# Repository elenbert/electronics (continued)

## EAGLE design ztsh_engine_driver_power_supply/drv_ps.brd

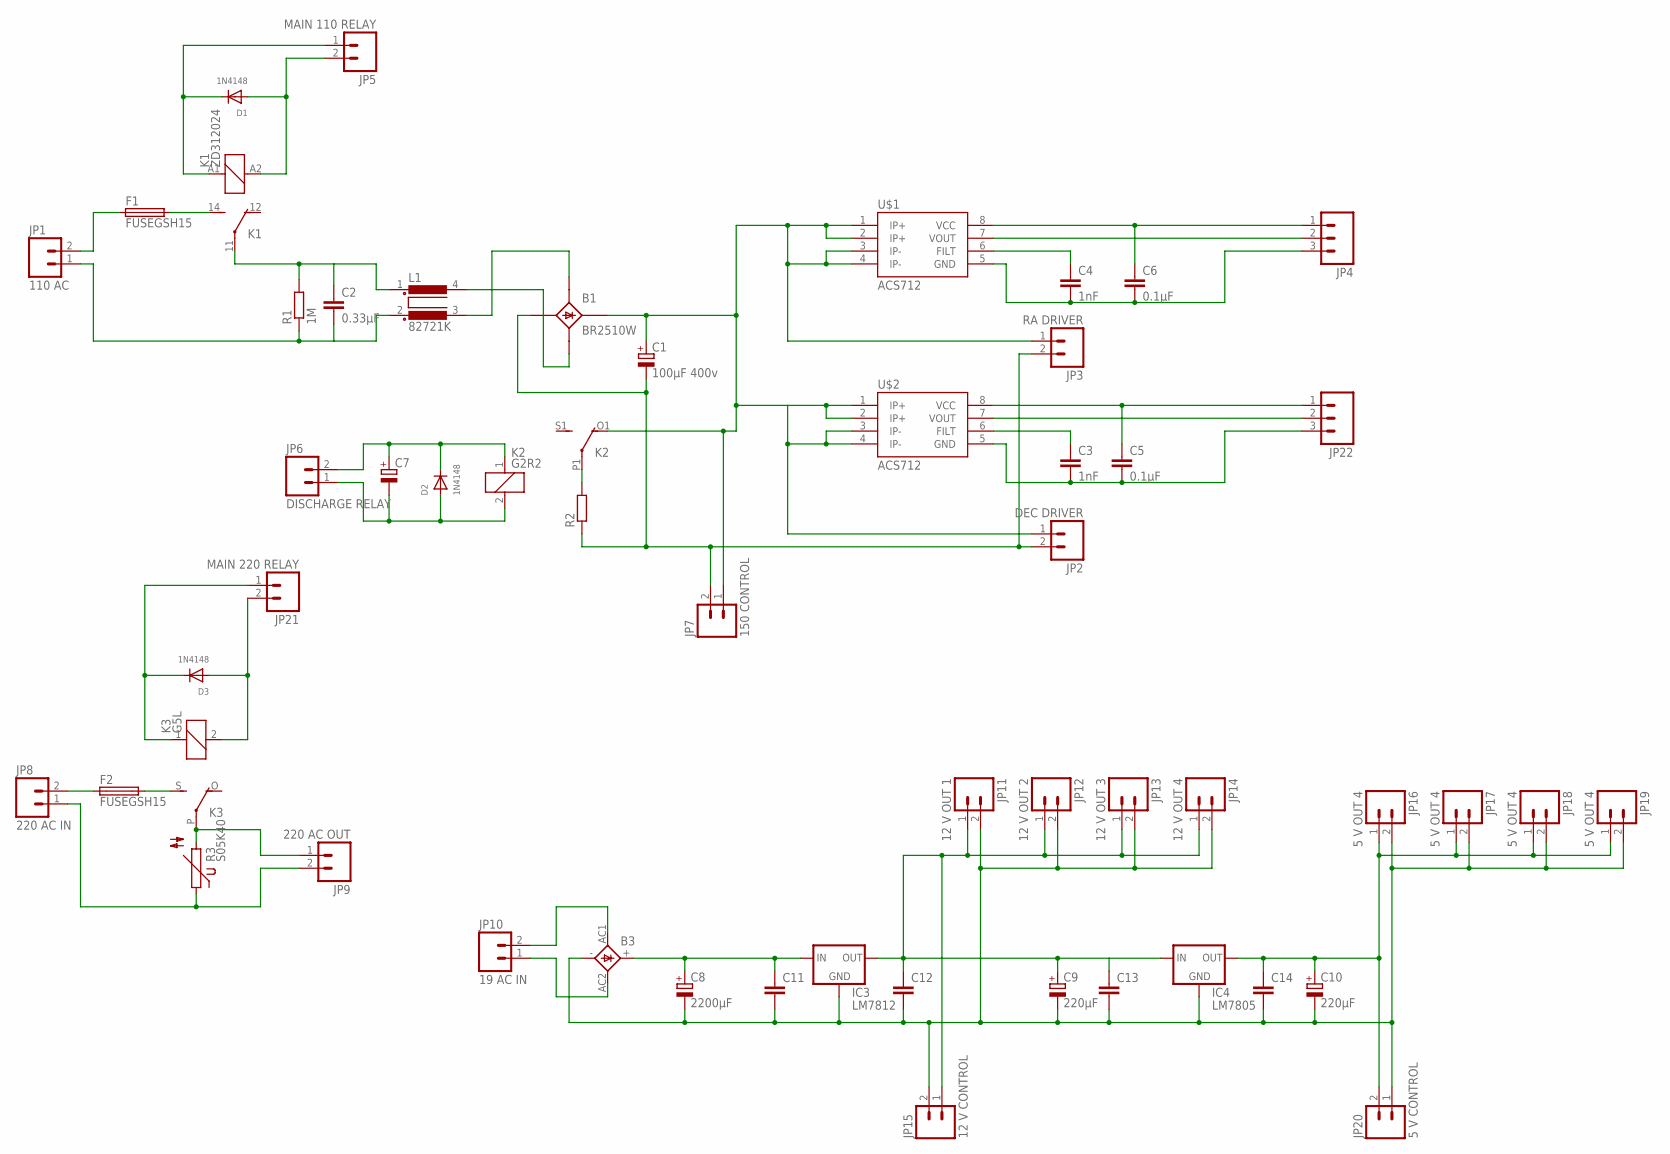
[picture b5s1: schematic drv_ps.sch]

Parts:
B1: BR2510W; B25A-
B3: GBPC1
C1: 100µF 400v; EB35D
C2: 0.33µF; C150-054X183
C3, C4: 1nF; C0805
C5, C6: 0.1µF; C0805
C7: CPOL-EUE2,5-6E; E2,5-6E
C8: 2200µF; E5-13
C9, C10: 220µF; E2,5-5
C11, C12, C13, C14: C-EUC0805; C0805
D1, D2, D3: 1N4148; DO-1N4148
F1, F2: FUSEGSH15; GSH15
IC3: LM7812; 78XXL
IC4: LM7805; 78XXL
JP1: 110 AC; SCREWTERMINAL-5MM-2
JP2: DEC DRIVER; SCREWTERMINAL-5MM-2
JP3: RA DRIVER; SCREWTERMINAL-5MM-2
JP4, JP22: M03POLAR; MOLEX-1X3
JP5: MAIN 110 RELAY; MOLEX-1X2
JP6: DISCHARGE RELAY; MOLEX-1X2
JP7: 150 CONTROL; MOLEX-1X2
JP8: 220 AC IN; SCREWTERMINAL-5MM-2
JP9: 220 AC OUT; SCREWTERMINAL-5MM-2
JP10: 19 AC IN; SCREWTERMINAL-5MM-2
JP11: 12 V OUT 1; JST-2-PTH-VERT
JP12: 12 V OUT 2; JST-2-PTH-VERT
JP13: 12 V OUT 3; JST-2-PTH-VERT
JP14: 12 V OUT 4; JST-2-PTH-VERT
JP15: 12 V CONTROL; 1X02
JP16, JP17, JP18, JP19: 5 V OUT 4; JST-2-PTH-VERT
JP20: 5 V CONTROL; 1X02
JP21: MAIN 220 RELAY; MOLEX-1X2
K1: ZD312024; ZD1
K2: G2R2
K3: G5L; G5LE
L1: 82721K
R1: 1M; 0411/15
R2: R-EU_VTA54; VTA54
R3: S05K40
U$1, U$2: ACS712; SO08

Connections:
5VCC: C10.+, C14.1, IC4.OUT, JP16.1, JP17.1, JP18.1, JP19.1, JP20.2
12VCC: C9.+, C12.1, C13.1, IC3.OUT, IC4.IN, JP11.1, JP12.1, JP13.1, JP14.1, JP15.1
19AC1: B3.AC2, JP10.1
19AC2: B3.AC1, JP10.2
110AC2: B1.AC2- (AC2), L1.4 (2)
110ACAF: F1.2, K1.14 (S)
110ACAR: C2.1, K1.11, L1.1, R1.2
110ACF1: B1.AC1- (AC1), L1.3 (4)
110ACG1: C2.2, JP1.1, L1.2 (3), R1.1
110ACPF: F1.1, JP1.2
110VC: B1.+1 (+), C1.+, JP2.1, JP3.1, JP7.1, K2.O1 (O), U$1.1 (IP+), U$1.2 (IP+), U$1.3 (IP-), U$1.4 (IP-), U$2.1 (IP+), U$2.2 (IP+), U$2.3 (IP-), U$2.4 (IP-)
AGND: B1.-1 (-), C1.-, JP2.2, JP3.2, JP7.2, R2.1
GND: B3.-, C8.-, C9.-, C10.-, C11.2, C12.2, C13.2, C14.2, IC3.GND, IC4.GND, JP11.2, JP12.2, JP13.2, JP14.2, JP15.2, JP16.2, JP17.2, JP18.2, JP19.2, JP20.1
unnamed: C4.1, U$1.6 (FILT)
unnamed: C4.2, C6.2, JP4.3, U$1.5 (GND)
unnamed: C3.1, U$2.6 (FILT)
unnamed: C6.1, JP4.1, U$1.8 (VCC)
unnamed: C3.2, C5.2, JP22.3, U$2.5 (GND)
unnamed: D1.C, JP5.1, K1.A1 (1)
unnamed: D1.A, JP5.2, K1.A2 (2)
unnamed: JP22.2, U$2.7 (VOUT)
unnamed: JP4.2, U$1.7 (VOUT)
unnamed: B3.+, C8.+, C11.1, IC3.IN
unnamed: C5.1, JP22.1, U$2.8 (VCC)
unnamed: K2.P1, R2.2
unnamed: C7.+, D2.C, JP6.2, K2.1
unnamed: C7.-, D2.A, JP6.1, K2.2
unnamed: JP9.1, K3.P, R3.2
unnamed: F2.1, JP8.2
unnamed: F2.2, K3.S
unnamed: JP8.1, JP9.2, R3.1
unnamed: D3.A, JP21.2, K3.2
unnamed: D3.C, JP21.1, K3.1

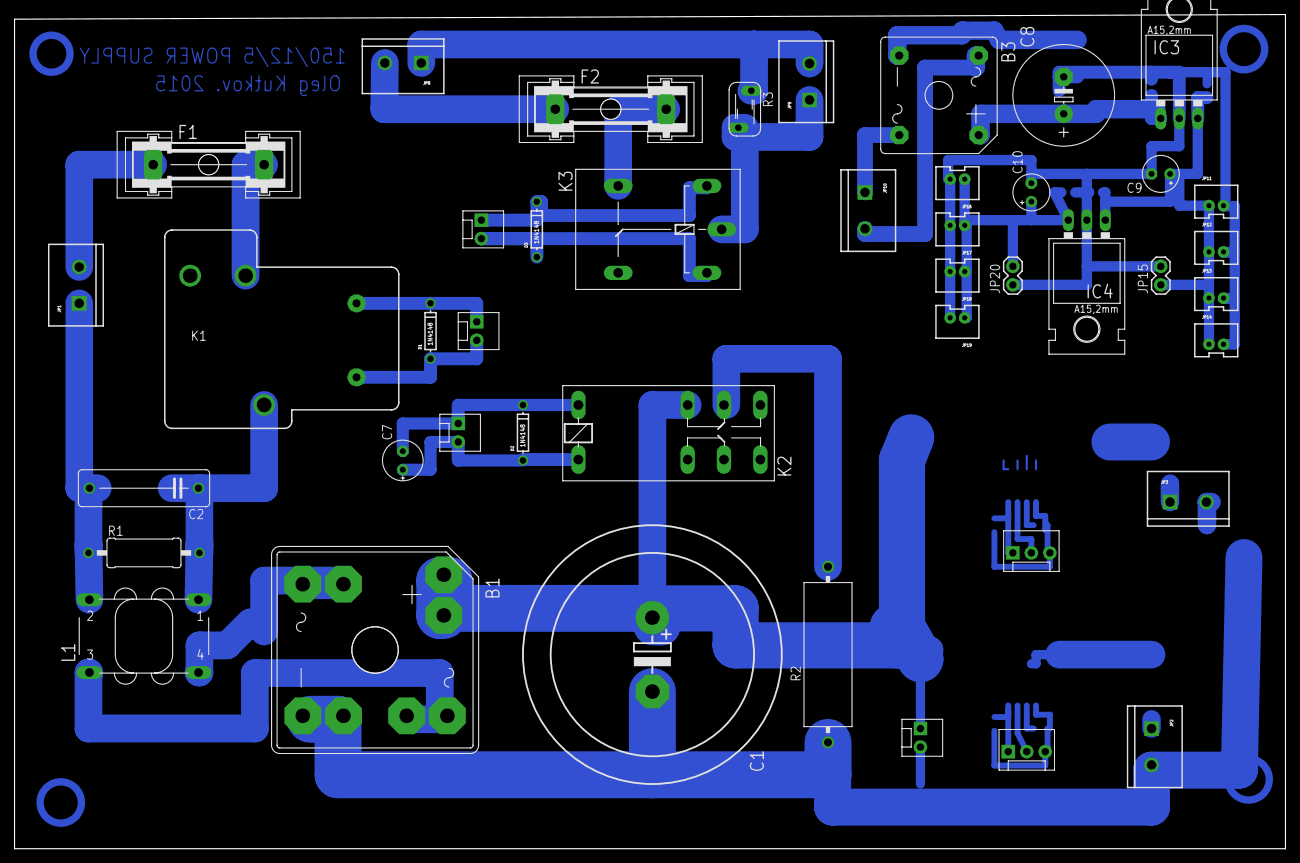
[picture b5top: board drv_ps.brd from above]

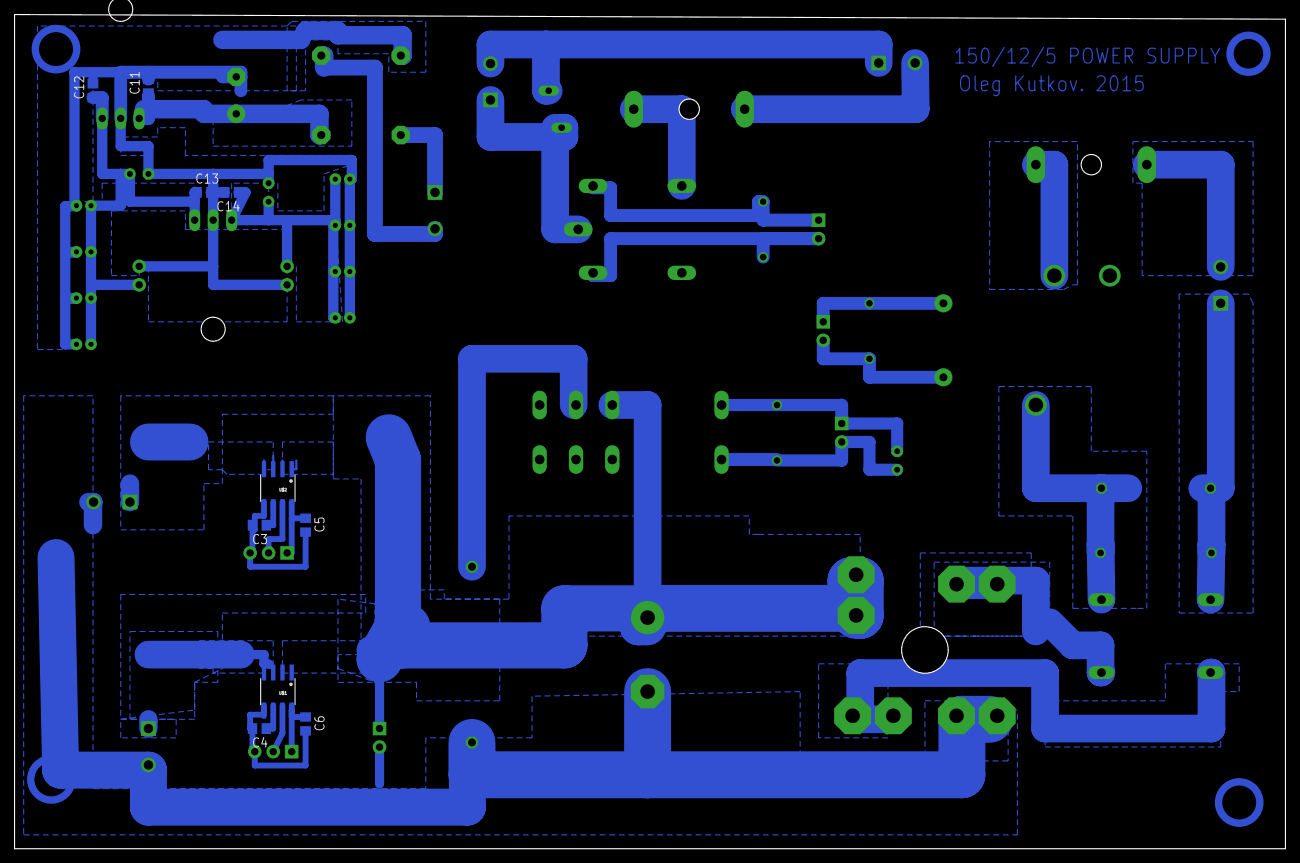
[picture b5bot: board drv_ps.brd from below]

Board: 2 copper layers, 174.6 x 114.6 mm, 54 parts (10 on the bottom side), 33 nets.

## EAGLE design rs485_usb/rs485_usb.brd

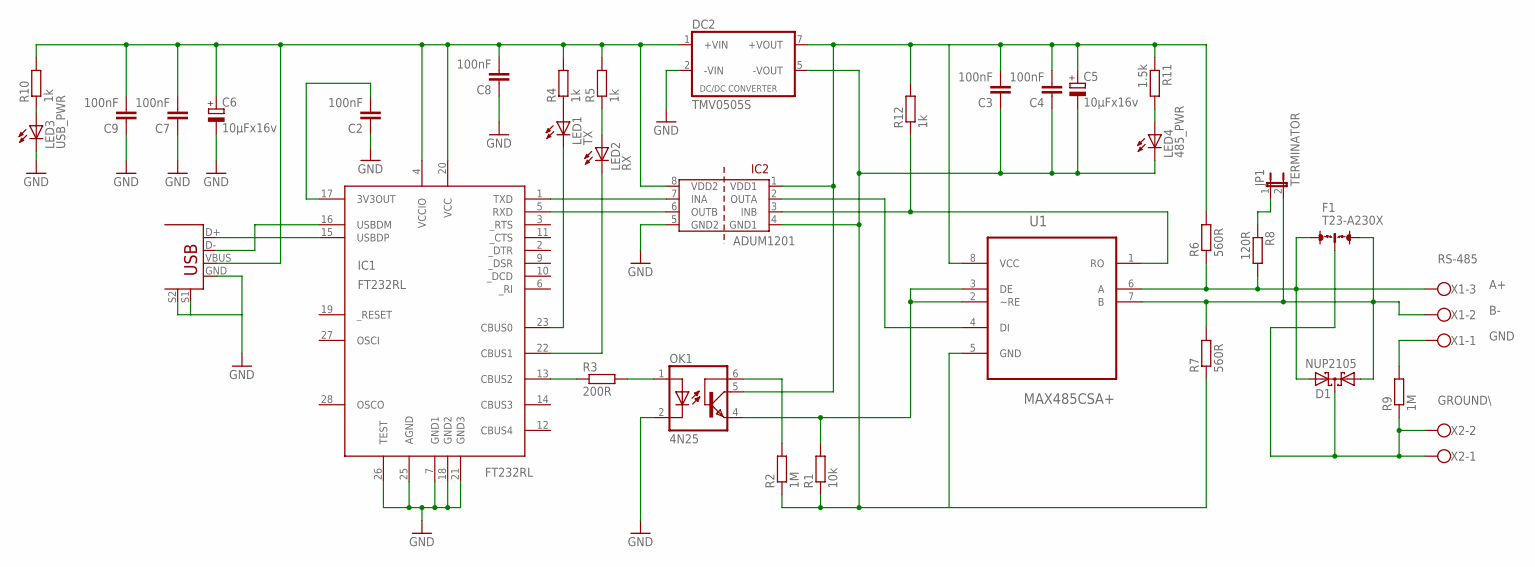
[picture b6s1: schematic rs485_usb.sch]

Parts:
C2: 100nF; C0603
C3, C4, C7, C8, C9: 100nF; C0805
C5, C6: 10µFx16v; E2,5-6E
D1: NUP2105; SOT23
DC2: TMV0505S; NMKXXXXSAC
F1: T23-A230X
IC1: FT232RL; SSOP28DB
IC2: ADUM1201; SO8
JP1: TERMINATOR; JP1
LED1: TX; LED3MM
LED2: RX; LED3MM
LED3: USB_PWR; LED3MM
LED4: 485_PWR; LED3MM
OK1: 4N25; DIL06
R1: 10k; 0204/5
R2: 1M; R0603
R3: 200R; R0603
R4, R5, R10, R12: 1k; R0805
R6, R7: 560R; R0603
R8: 120R; R0603
R9: 1M; 0207/2V
R11: 1.5k; R0805
U1: MAX485CSA+; SOIC127P600X175-8N
U$1: USB+SHIELD; USB-B-PTH
X1: W237-103
X2: W237-102

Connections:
GND: C2.1, C6.-, C7.1, C8.1, C9.1, DC2.2 (-VIN), IC1.7 (GND1), IC1.18 (GND2), IC1.21 (GND3), IC1.25 (AGND), IC1.26 (TEST), IC2.5 (GND2), LED3.K (C), OK1.2 (C), U$1.GND, U$1.S1, U$1.S2
GROUND: D1.3 (C), F1.2, R9.1, X2.1, X2.2
unnamed: IC1.15 (USBDP), U$1.D+
unnamed: IC1.16 (USBDM), U$1.D-
unnamed: C6.+, C7.2, C8.2, C9.2, DC2.1 (+VIN), IC1.4 (VCCIO), IC1.20 (VCC), IC2.8 (VDD2), R4.2, R5.2, R10.2, U$1.VBUS
unnamed: IC1.1 (TXD), IC2.7 (INA)
unnamed: IC1.5 (RXD), IC2.6 (OUTB)
unnamed: OK1.4 (EMI), R1.2, U1.2 (~RE), U1.3 (DE)
unnamed: IC2.2 (OUTA), U1.4 (DI)
unnamed: IC2.3 (INB), R12.1, U1.1 (RO)
unnamed: JP1.1, R8.1
unnamed: C3.2, C4.2, C5.+, DC2.7 (+VOUT), IC2.1 (VDD1), OK1.5 (COL), R6.2, R11.1, R12.2, U1.8 (VCC)
unnamed: OK1.6 (BAS), R2.2
unnamed: OK1.1 (A), R3.2
unnamed: IC1.13 (CBUS2), R3.1
unnamed: IC1.23 (CBUS0), LED1.K (C)
unnamed: IC1.22 (CBUS1), LED2.K (C)
unnamed: LED1.A, R4.1
unnamed: LED2.A, R5.1
unnamed: C2.2, IC1.17 (3V3OUT)
unnamed: C3.1, C4.1, C5.-, DC2.5 (-VOUT), IC2.4 (GND1), LED4.K (C), R1.1, R2.1, R7.1, U1.5 (GND)
unnamed: D1.2 (A2), F1.1, R6.1, R8.2, U1.6 (A), X1.3
unnamed: D1.1 (A1), F1.3, JP1.2, R7.2, U1.7 (B), X1.2
unnamed: R9.2, X1.1
unnamed: LED4.A, R11.2
unnamed: LED3.A, R10.1

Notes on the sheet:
GND
RS-485
GROUND\
ADUM1201
FT232RL

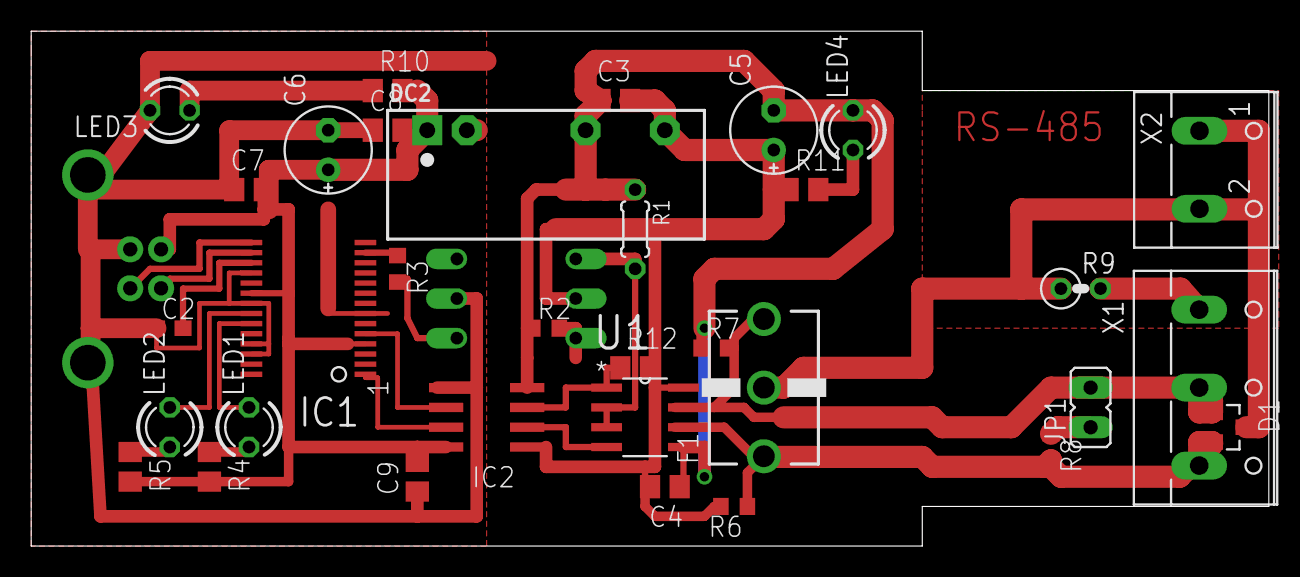
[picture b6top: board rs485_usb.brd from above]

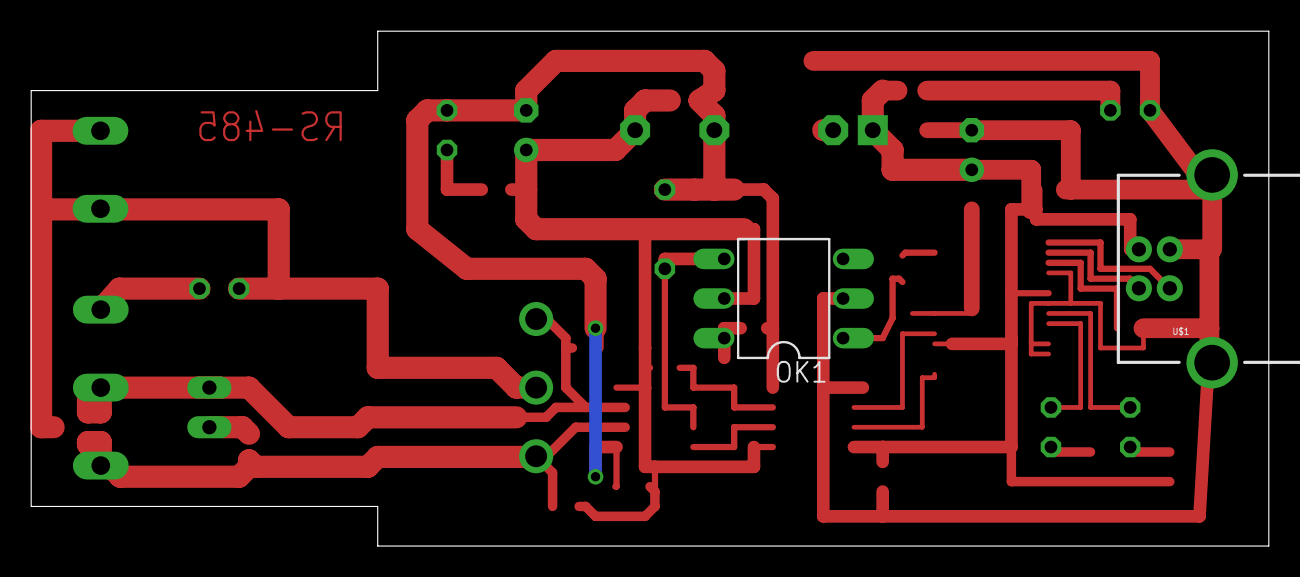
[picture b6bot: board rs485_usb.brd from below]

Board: 2 copper layers, 79.4 x 33.0 mm, 35 parts (2 on the bottom side), 26 nets.

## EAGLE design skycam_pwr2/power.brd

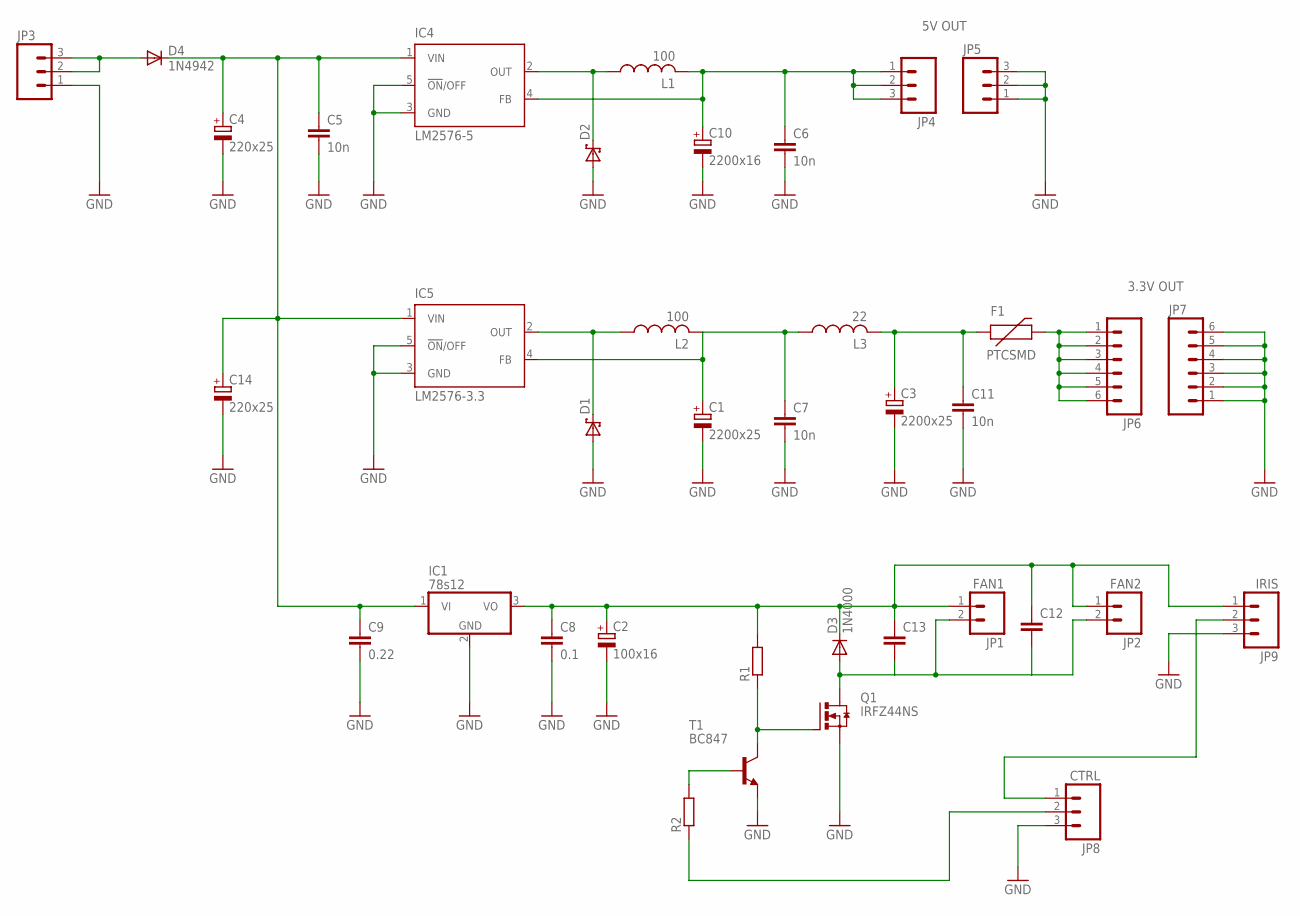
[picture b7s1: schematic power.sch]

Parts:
C1, C3: 2200x25; E3,5-10
C2: 100x16; E2,5-7
C4, C14: 220x25; E3,5-10
C5, C6, C7, C11: 10n; 0805
C8: 0.1; 0805
C9: 0.22; 0805
C10: 2200x16; E3,5-10
C12, C13: C-EUC0805K; C0805K
D1, D2: DS_E2L; E2LINE
D3: 1N4000; DO41-10
D4: 1N4942; DO41-10
F1: PTCSMD; PTC-1206
IC1: 78s12; TO220H
IC4: LM2576-5; TO263-5
IC5: LM2576-3.3; TO263-5
JP1: FAN1; JST-2-PTH-VERT
JP2: FAN2; JST-2-PTH-VERT
JP3: M03JST-PTH-VERT; JST-3-PTH-VERT
JP4, JP5: M03LOCK; 1X03_LOCK
JP6, JP7: M06LOCK; 1X06_LOCK
JP8: CTRL; 1X03
JP9: IRIS; 1X03
L1, L2: 100; L8530M
L3: 22; L8530M
Q1: IRFZ44NS; D2PACK
R1, R2: R-EU_R0805; R0805
T1: BC847; SOT23

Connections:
GND: C1.-, C2.-, C3.-, C4.-, C5.2, C6.2, C7.2, C8.2, C9.2, C10.-, C11.2, C14.-, D1.2 (A), D2.2 (A), IC1.2 (GND), IC4.3 (GND), IC4.5 (!ON!/OFF), IC5.3 (GND), IC5.5 (!ON!/OFF), JP3.1, JP5.1, JP5.2, JP5.3, JP7.1, JP7.2, JP7.3, JP7.4, JP7.5, JP7.6, JP8.3, JP9.3, Q1.3 (S), T1.2 (E)
unnamed: C12.2, C13.2, D3.A, JP1.2, JP2.2, Q1.2 (D)
unnamed: C4.+, C5.1, C9.1, C14.+, D4.C, IC1.1 (VI), IC4.1 (VIN), IC5.1 (VIN)
unnamed: D2.1 (K), IC4.2 (OUT), L1.1
unnamed: JP8.2, R2.1
unnamed: C6.1, C10.+, IC4.4 (FB), JP4.1, JP4.2, JP4.3, L1.2
unnamed: Q1.1 (G), R1.1, T1.3 (C)
unnamed: R2.2, T1.1 (B)
unnamed: D1.1 (K), IC5.2 (OUT), L2.1
unnamed: C2.+, C8.1, C12.1, C13.1, D3.C, IC1.3 (VO), JP1.1, JP2.1, JP9.1, R1.2
unnamed: D4.A, JP3.2, JP3.3
unnamed: JP8.1, JP9.2
unnamed: C1.+, C7.1, IC5.4 (FB), L2.2, L3.1
unnamed: F1.2, JP6.1, JP6.2, JP6.3, JP6.4, JP6.5, JP6.6
unnamed: C3.+, C11.1, F1.1, L3.2

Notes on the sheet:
5V OUT
3.3V OUT

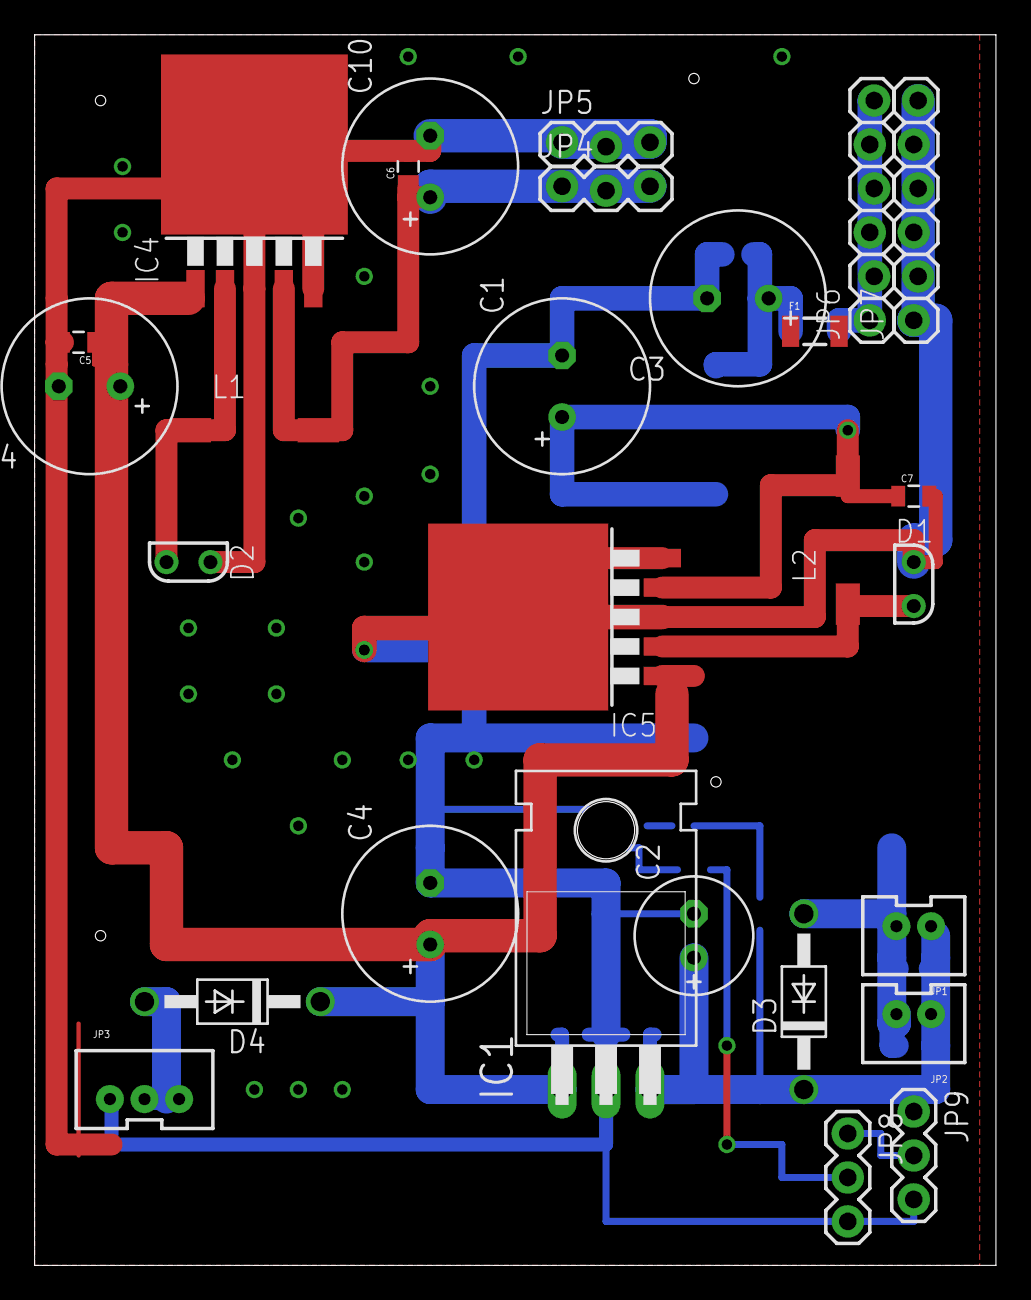
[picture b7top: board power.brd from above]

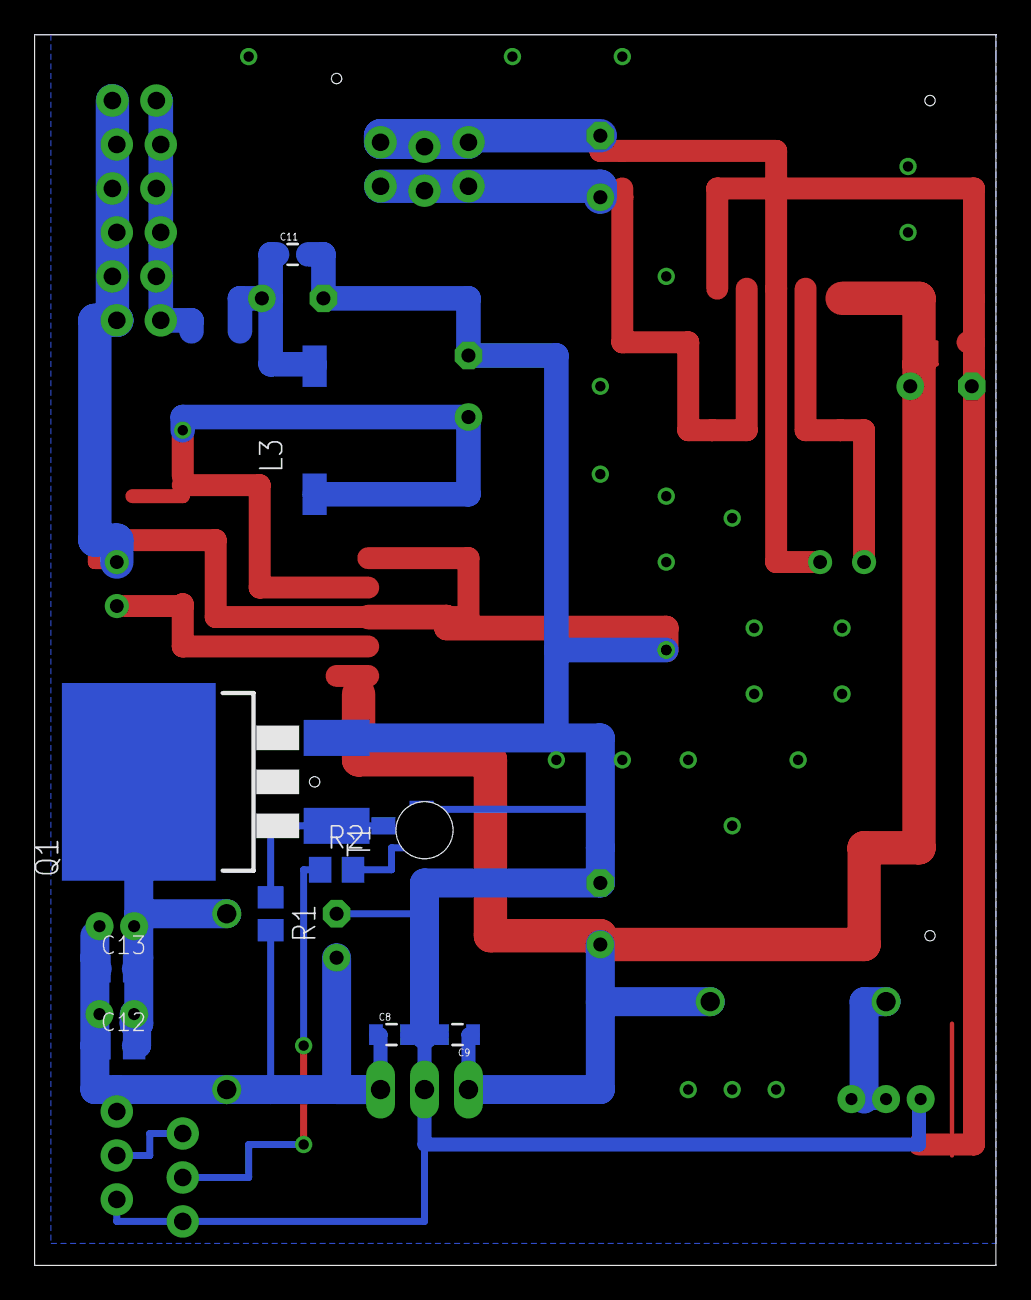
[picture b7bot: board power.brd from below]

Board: 2 copper layers, 55.5 x 71.1 mm, 38 parts (10 on the bottom side), 15 nets.

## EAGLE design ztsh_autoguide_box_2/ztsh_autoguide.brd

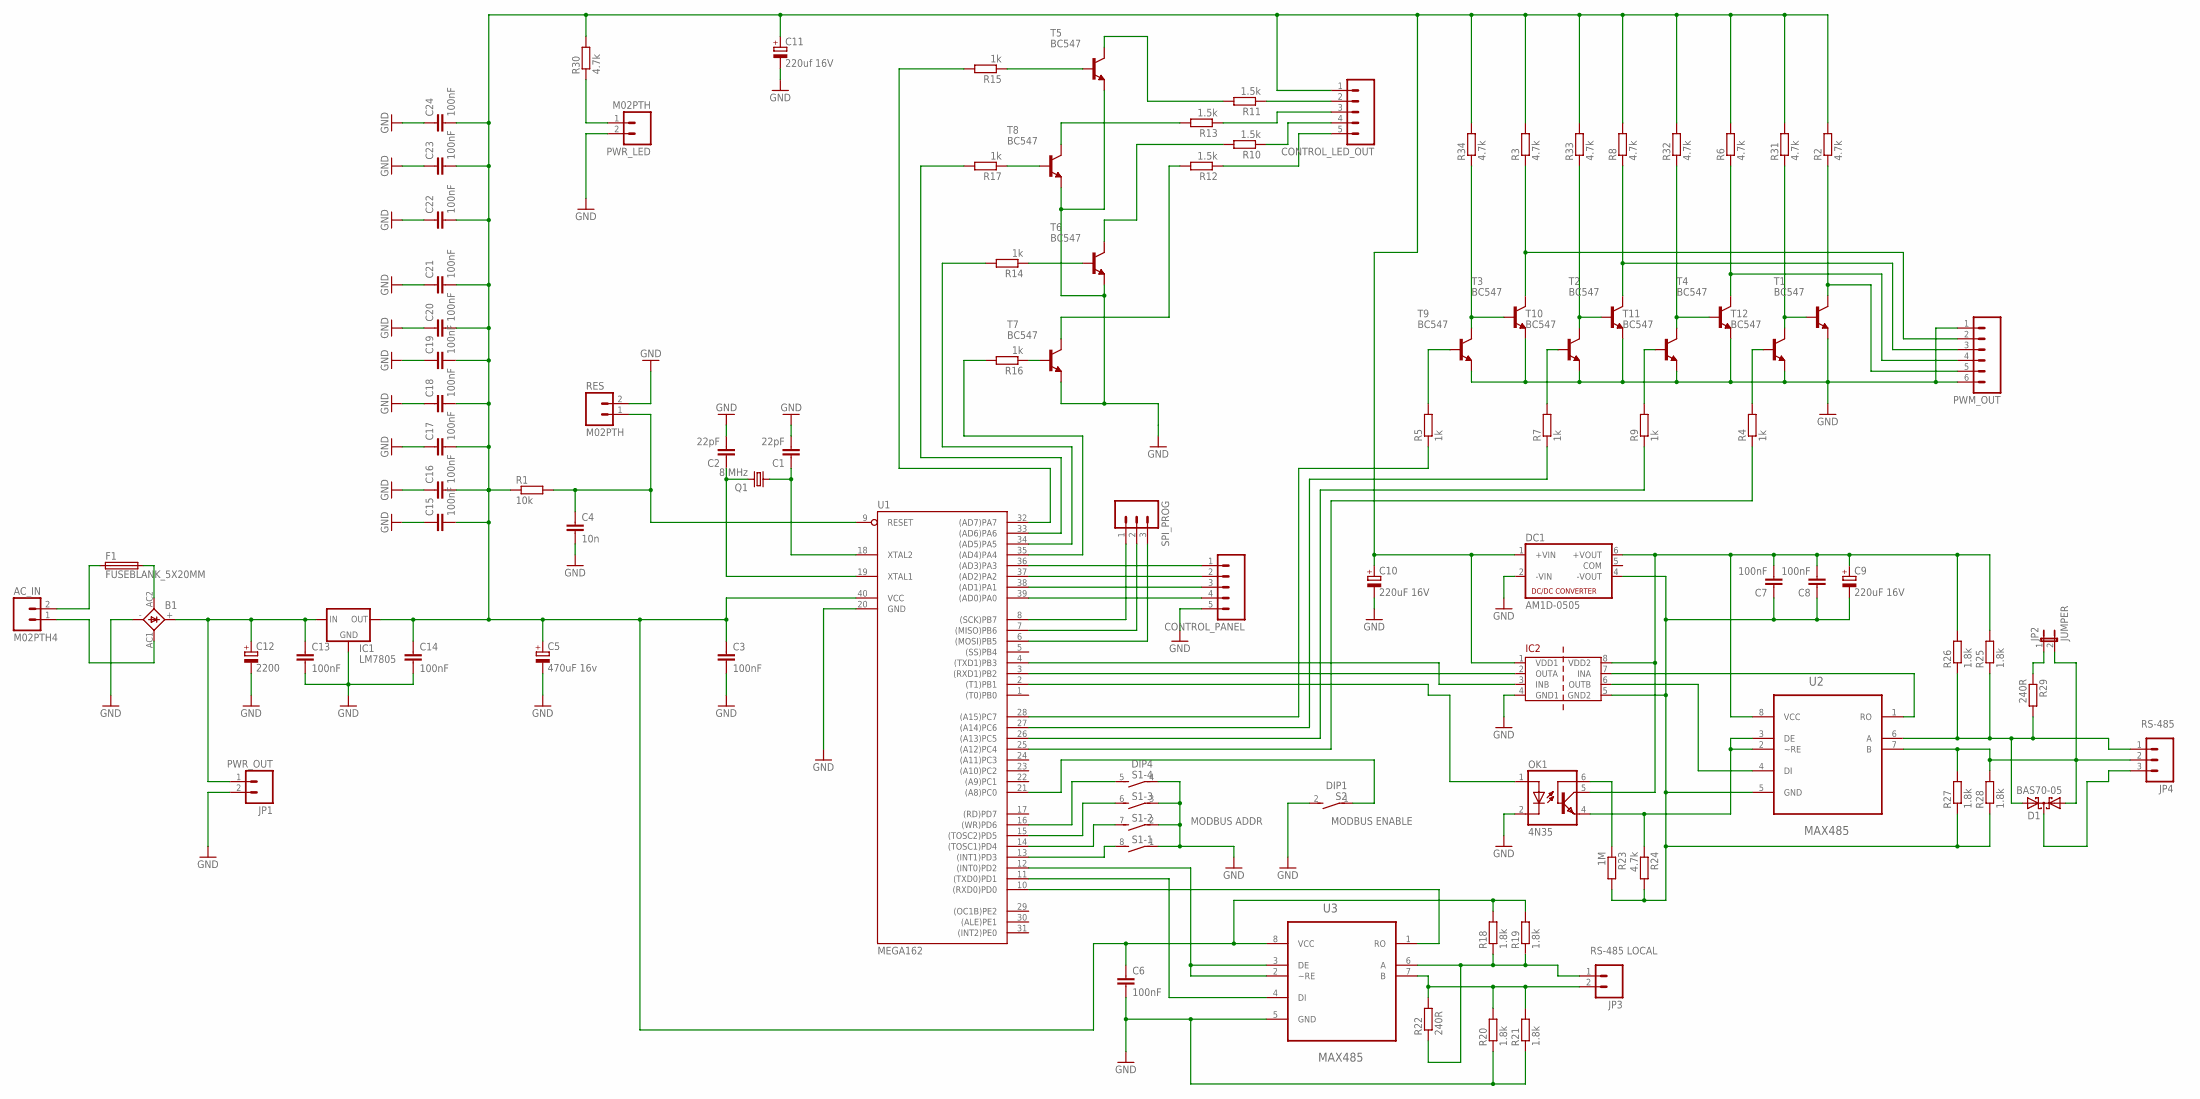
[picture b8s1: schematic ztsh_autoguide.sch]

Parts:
AC_IN: M02PTH4; 1X02_XTRA_BIG
B1: KBL
C1, C2: 22pF; C025-024X044
C3, C6, C7, C8, C13, C14, C15, C16, C17, C18, C19, C20, C21, C22, C23, C24: 100nF; C0805
C4: 10n; C0805
C5: 470uF 16v; E2-5
C9, C10: 220uF 16V; E2-5
C11: 220uf 16V; E2-5
C12: 2200; E3,5-10
CONTROL_LED_OUT: M05LOCK; 1X05_LOCK
CONTROL_PANEL: M05LOCK; 1X05_LOCK
D1: BAS70-05; SOT23
DC1: AM1D-0505; NMA
F1: FUSEBLANK_5X20MM; FUSE_HOLDER_5X20MM
IC1: LM7805; TO-220-ALT
IC2: ADUM1201; SO8
JP1: PWR_OUT; 1X02_LOCK_LONGPADS
JP2: JUMPER; JP1
JP3: M02JST-PTH-VERT; JST-2-PTH-VERT
JP4: M03JST-PTH-VERT; JST-3-PTH-VERT
OK1: 4N35; DIL06
PWM_OUT: M06LOCK; 1X06_LOCK
PWR_LED: M02PTH; 1X02
Q1: 8 MHz; HC18U-V
R1: 10k; 0207/10
R2, R3, R6, R8, R24, R31, R32, R33, R34: 4.7k; 0204/7
R4, R5, R7, R9, R14, R15, R16, R17: 1k; 0204/7
R10, R11, R12, R13: 1.5k; 0204/7
R18, R19, R20, R21, R25, R26, R27, R28: 1.8k; R0805
R22, R29: 240R; R0805
R23: 1M; 0204/7
R30: 4.7k; 0207/10
RES: M02PTH; 1X02
S1: DIP4; DIP04S
S2: DIP1; DS-01
SPI_PROG: M03LOCK; 1X03_LOCK
T1, T2, T3, T4, T5, T6, T7, T8, T9, T10, T11, T12: BC547; TO92
U1: MEGA162; DIL40
U2, U3: MAX485; SOIC127P600X175-8N

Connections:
GND: B1.-, C1.2, C2.2, C3.2, C4.2, C5.-, C6.2, C10.-, C11.-, C12.-, C13.2, C14.2, C15.1, C16.1, C17.1, C18.1, C19.1, C20.1, C21.1, C22.1, C23.1, C24.1, CONTROL_PANEL.5, DC1.2 (-VIN), IC1.GND, IC2.4 (GND1), JP1.2, OK1.2 (C), PWM_OUT.1, PWM_OUT.6, PWR_LED.2, R20.1, R21.1, RES.2, S1.1, S1.2 (1), S1.3 (1), S1.4 (1), S2.2, T1.1 (E), T2.1 (E), T3.1 (E), T4.1 (E), T5.1 (E), T6.1 (E), T7.1 (E), T8.1 (E), T9.1 (E), T10.1 (E), T11.1 (E), T12.1 (E), U1.20 (GND), U3.5 (GND)
GND_ISOL: C7.1, C8.1, C9.-, DC1.4 (-VOUT), IC2.5 (GND2), R23.2, R24.2, R27.1, R28.1, U2.5 (GND)
unnamed: C2.1, Q1.2, U1.19 (XTAL1)
unnamed: C1.1, Q1.1, U1.18 (XTAL2)
unnamed: C4.1, R1.2, RES.1, U1.9 (RESET)
unnamed: U1.11 ((TXD0)PD1), U3.4 (DI)
unnamed: U1.12 ((INT0)PD2), U3.2 (~RE), U3.3 (DE)
unnamed: U1.10 ((RXD0)PD0), U3.1 (RO)
unnamed: R7.2, T10.2 (B)
unnamed: R15.2, U1.32 ((AD7)PA7)
unnamed: JP3.1, R18.1, R19.1, R22.1, U3.6 (A)
unnamed: JP3.2, R20.2, R21.2, R22.2, U3.7 (B)
unnamed: R17.2, U1.33 ((AD6)PA6)
unnamed: R14.2, U1.34 ((AD5)PA5)
unnamed: R16.1, T7.2 (B)
unnamed: R16.2, U1.35 ((AD4)PA4)
unnamed: B1.+, C12.+, C13.1, IC1.IN, JP1.1
unnamed: AC_IN.1, B1.AC1 (AC2)
unnamed: AC_IN.2, F1.1
unnamed: IC2.2 (OUTA), U1.3 ((RXD1)PB2)
unnamed: R14.1, T6.2 (B)
unnamed: CONTROL_LED_OUT.2, R11.1
unnamed: CONTROL_LED_OUT.3, R13.1
unnamed: CONTROL_LED_OUT.4, R10.1
unnamed: CONTROL_LED_OUT.5, R12.1
unnamed: R11.2, T5.3 (C)
unnamed: R13.2, T8.3 (C)
unnamed: R10.2, T6.3 (C)
unnamed: R12.2, T7.3 (C)
unnamed: R17.1, T8.2 (B)
unnamed: R15.1, T5.2 (B)
unnamed: B1.AC2 (AC1), F1.2
unnamed: IC2.3 (INB), U1.4 ((TXD1)PB3)
unnamed: R5.2, T9.2 (B)
unnamed: SPI_PROG.1, U1.8 ((SCK)PB7)
unnamed: SPI_PROG.2, U1.7 ((MISO)PB6)
unnamed: SPI_PROG.3, U1.6 ((MOSI)PB5)
unnamed: IC2.7 (INA), U2.1 (RO)
unnamed: D1.3 (C), JP4.3
unnamed: IC2.6 (OUTB), U2.4 (DI)
unnamed: R9.2, T11.2 (B)
unnamed: JP2.1, R29.1
unnamed: OK1.4 (EMI), R24.1, U2.2 (~RE), U2.3 (DE)
unnamed: CONTROL_PANEL.1, U1.36 ((AD3)PA3)
unnamed: CONTROL_PANEL.2, U1.37 ((AD2)PA2)
unnamed: OK1.1 (A), U1.2 ((T1)PB1)
unnamed: D1.2 (A2), JP4.1, R25.1, R26.1, R29.2, U2.6 (A)
unnamed: D1.1 (A1), JP2.2, JP4.2, R27.2, R28.2, U2.7 (B)
unnamed: R4.2, T12.2 (B)
unnamed: OK1.6 (BAS), R23.1
unnamed: CONTROL_PANEL.3, U1.38 ((AD1)PA1)
unnamed: CONTROL_PANEL.4, U1.39 ((AD0)PA0)
unnamed: PWR_LED.1, R30.1
unnamed: PWM_OUT.5, R2.1, T1.3 (C)
unnamed: PWM_OUT.4, R6.1, T4.3 (C)
unnamed: PWM_OUT.3, R8.1, T2.3 (C)
unnamed: PWM_OUT.2, R3.1, T3.3 (C)
unnamed: R34.1, T3.2 (B), T9.3 (C)
unnamed: R33.1, T2.2 (B), T10.3 (C)
unnamed: R32.1, T4.2 (B), T11.3 (C)
unnamed: R31.1, T1.2 (B), T12.3 (C)
unnamed: R5.1, U1.28 ((A15)PC7)
unnamed: R7.1, U1.27 ((A14)PC6)
unnamed: R9.1, U1.26 ((A13)PC5)
unnamed: R4.1, U1.25 ((A12)PC4)
unnamed: S1.8 (2), U1.13 ((INT1)PD3)
unnamed: S1.7 (2), U1.14 ((TOSC1)PD4)
unnamed: S1.6 (2), U1.15 ((TOSC2)PD5)
unnamed: S1.5 (2), U1.16 ((WR)PD6)
unnamed: S2.1, U1.21 ((A8)PC0)
VCC: C3.1, C5.+, C6.1, C10.+, C11.+, C14.1, C15.2, C16.2, C17.2, C18.2, C19.2, C20.2, C21.2, C22.2, C23.2, C24.2, CONTROL_LED_OUT.1, DC1.1 (+VIN), IC1.OUT, IC2.1 (VDD1), R1.1, R2.2, R3.2, R6.2, R8.2, R18.2, R19.2, R30.2, R31.2, R32.2, R33.2, R34.2, U1.40 (VCC), U3.8 (VCC)
VCC_ISOL: C7.2, C8.2, C9.+, DC1.6 (+VOUT), IC2.8 (VDD2), OK1.5 (COL), R25.2, R26.2, U2.8 (VCC)

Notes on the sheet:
RS-485 LOCAL
RS-485
MODBUS ADDR
MODBUS ENABLE

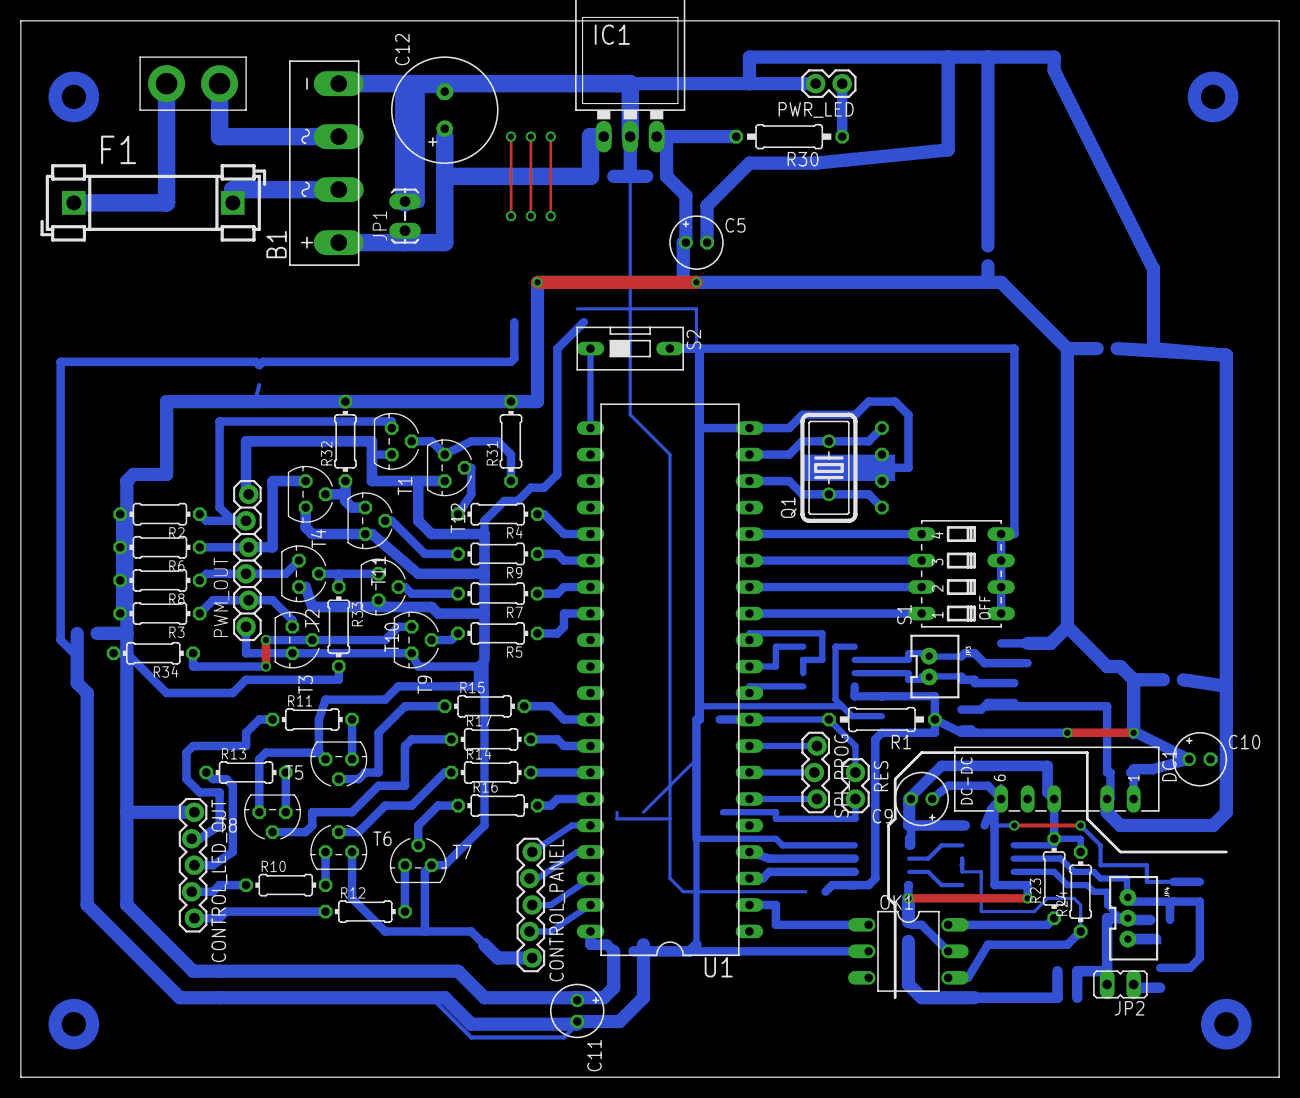
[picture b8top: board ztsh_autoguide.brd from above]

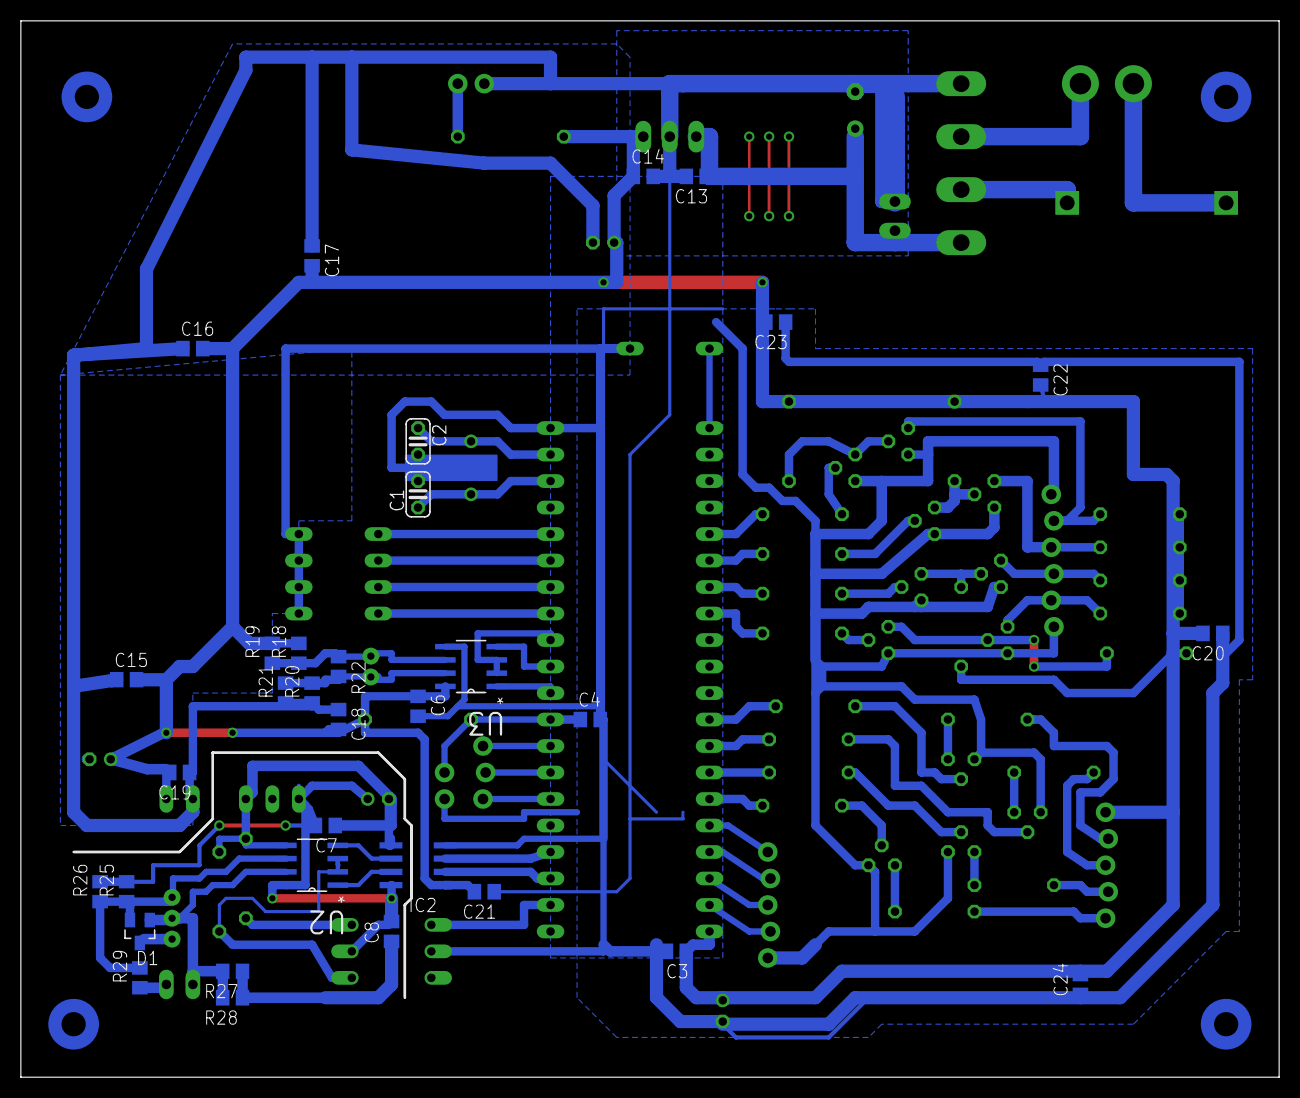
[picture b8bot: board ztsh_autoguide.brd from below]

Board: 2 copper layers, 120.6 x 101.3 mm, 94 parts (33 on the bottom side), 72 nets.

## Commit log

2017-01-17 inital upload of the schematics
2017-01-17 readme update
2017-01-19 board update
2017-02-06 board update...
2017-02-07 board update (near finish, hope...)
2017-02-13 schematic update using 74hc00
